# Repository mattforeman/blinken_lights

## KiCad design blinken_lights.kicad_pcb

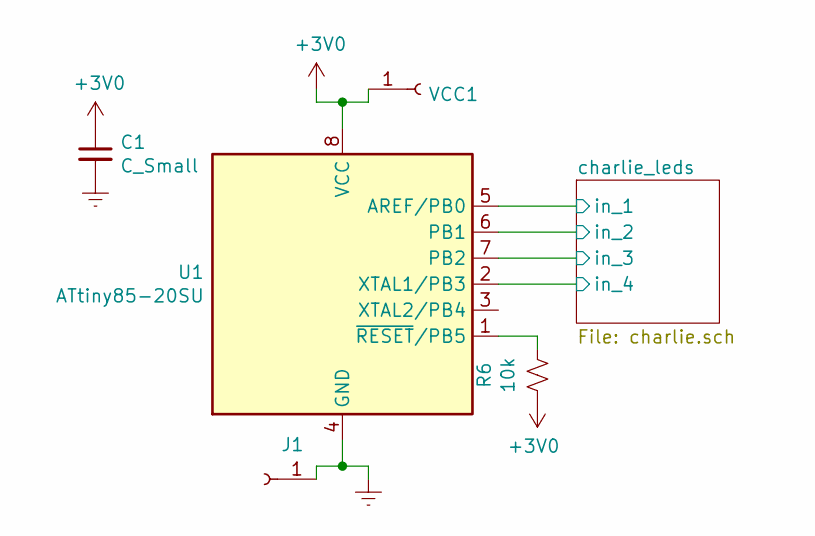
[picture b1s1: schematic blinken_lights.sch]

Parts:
C1: C_Small; R_0805_2012Metric_Pad1.15x1.40mm_HandSolder
J1: Conn_01x01_Female; Pin_D1.0mm_L10.0mm_LooseFit
R6: 10k; R_0805_2012Metric_Pad1.15x1.40mm_HandSolder
U1: ATtiny85-20SU; SOIJ-8_5.3x5.3mm_P1.27mm
VCC1: Conn_01x01_Female; Pin_D1.0mm_L10.0mm_LooseFit

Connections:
+3V0: C1.1, R6.2, U1.8 (VCC), VCC1.1
/charlie_leds/in_1: U1.5 (AREF/PB0); also elsewhere on the board
/charlie_leds/in_2: U1.6 (PB1); also elsewhere on the board
/charlie_leds/in_3: U1.7 (PB2); also elsewhere on the board
/charlie_leds/in_4: U1.2 (XTAL1/PB3); also elsewhere on the board
Earth: C1.2, J1.1, U1.4 (GND)
unnamed: R6.1, U1.1 (~RESET~/PB5)

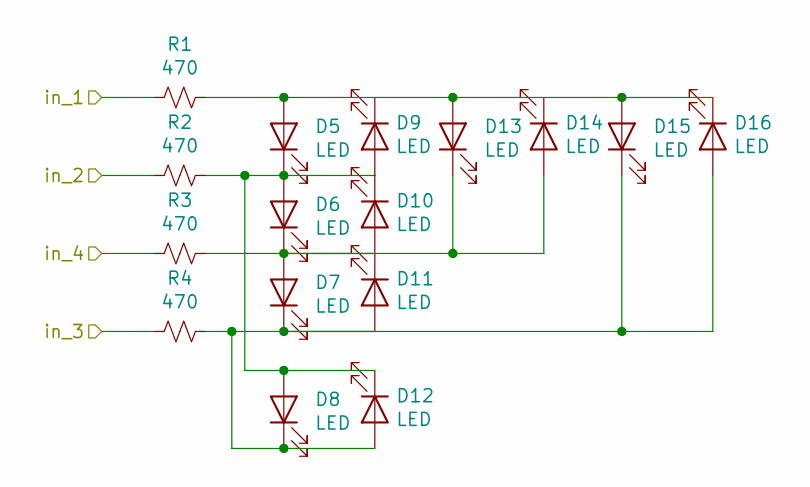
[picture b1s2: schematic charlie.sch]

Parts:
D5, D6, D7, D8, D9, D10, D11, D12, D13, D14, D15, D16: LED; D_0805_2012Metric_Pad1.15x1.40mm_HandSolder
R1, R2, R3, R4: 470; R_0805_2012Metric_Pad1.15x1.40mm_HandSolder

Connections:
/charlie_leds/in_1: R1.2; also elsewhere on the board
/charlie_leds/in_2: R2.2; also elsewhere on the board
/charlie_leds/in_3: R4.2; also elsewhere on the board
/charlie_leds/in_4: R3.2; also elsewhere on the board
unnamed: D5.1 (K), D6.2 (A), D8.2 (A), D9.2 (A), D10.1 (K), D12.1 (K), R2.1
unnamed: D6.1 (K), D7.2 (A), D10.2 (A), D11.1 (K), D13.1 (K), D14.2 (A), R3.1
unnamed: D7.1 (K), D8.1 (K), D11.2 (A), D12.2 (A), D15.1 (K), D16.2 (A), R4.1
unnamed: D5.2 (A), D9.1 (K), D13.2 (A), D14.1 (K), D15.2 (A), D16.1 (K), R1.1

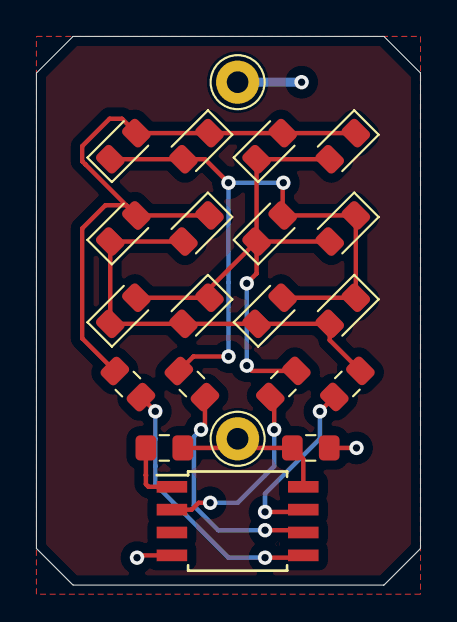
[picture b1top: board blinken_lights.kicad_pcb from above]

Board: 2 copper layers, 21.3 x 30.5 mm, 21 parts (0 on the bottom side), 11 nets.

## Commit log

2019-09-06 major work
    done?
    art needed
